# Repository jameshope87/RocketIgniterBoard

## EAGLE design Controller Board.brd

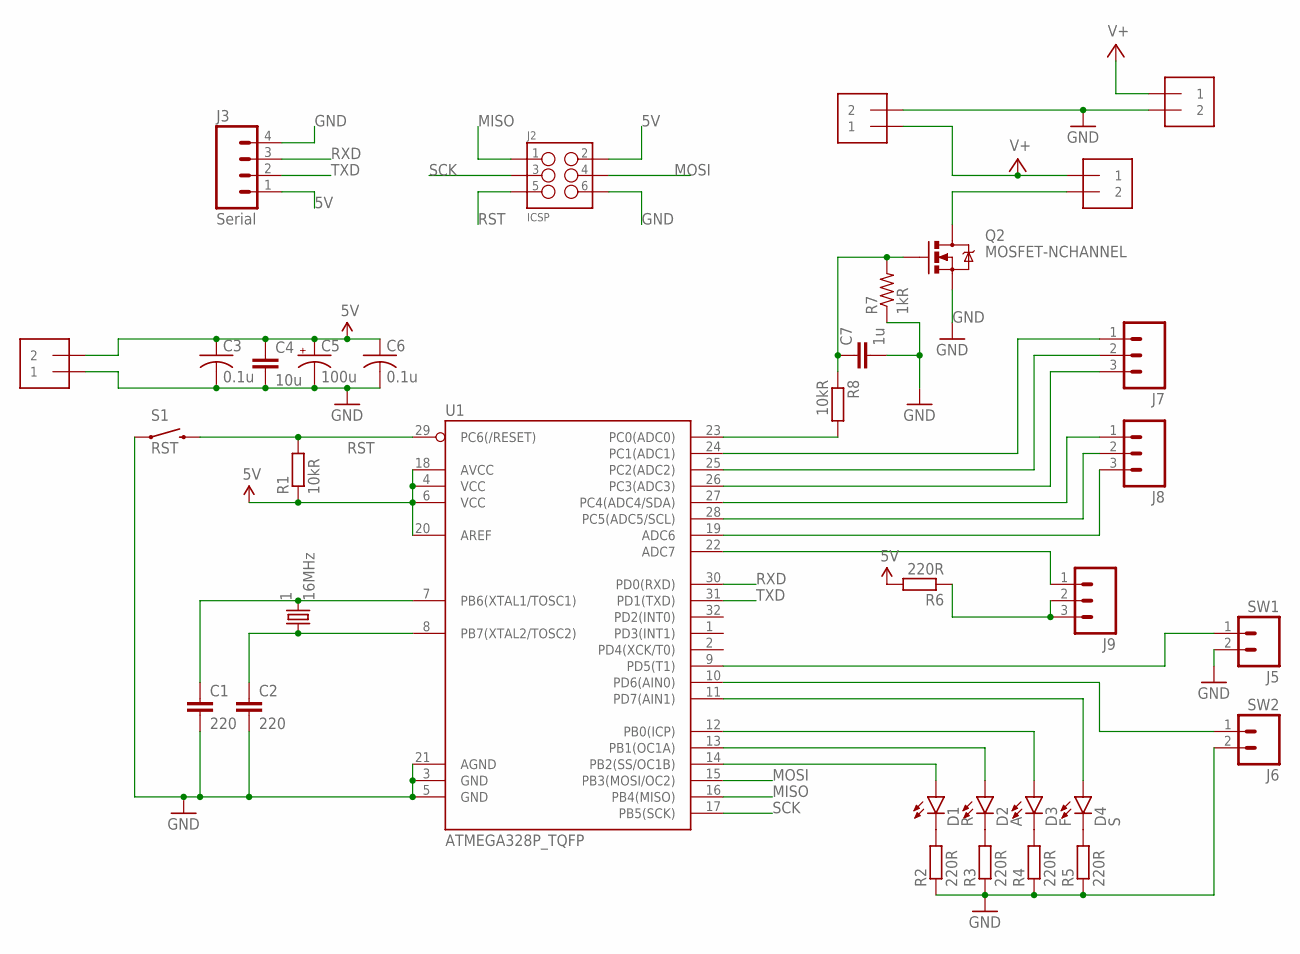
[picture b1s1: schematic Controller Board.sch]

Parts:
1: 16MHz; CRYSTAL-OSC-SMD-5X3.2
C1, C2: 220; C0603
C3, C6: 0.1u; C0603
C4: 10u; 0603-CAP
C5: 100u; PANASONIC_D
C7: 1u; 0603-CAP
D1: R; LED5MM
D2: A; LED5MM
D3: F; LED5MM
D4: S; LED5MM
FAN: FAN; 1X2-3.5MM
HV: HV; 1X2-3.5MM
J2: ICSP; 2X3
J3: Serial; 1X04
J5: SW1; 1X02_POLAR
J6: SW2; 1X02_POLAR
J7, J8, J9: M03PTH; 1X03
POWER: +5V; 1X2-3.5MM
Q2: MOSFET-NCHANNEL; TO220V
R1, R8: 10kR; R0603
R2, R3, R4, R5, R6: 220R; R0603
R7: 1kR; 0603-RES
S1: RST; TACTILE-SWITCH-1101NE
U1: ATMEGA328P_TQFP; TQFP32-08
V+: V+; 1X2-3.5MM

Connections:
5V: C3.1, C4.1, C5.+, C6.1, J2.2, J3.1, POWER.2, R1.1, R6.2, U1.4 (VCC), U1.6 (VCC), U1.18 (AVCC), U1.20 (AREF)
A: J7.1, U1.24 (PC1(ADC1))
B: J7.2, U1.25 (PC2(ADC2))
C: J7.3, U1.26 (PC3(ADC3))
D: J8.1, U1.27 (PC4(ADC4/SDA))
E: J8.2, U1.28 (PC5(ADC5/SCL))
F: J8.3, U1.19 (ADC6)
G: J9.1, U1.22 (ADC7)
GND: C1.2, C2.2, C3.2, C4.2, C5.-, C6.2, C7.2, FAN.2, J2.6, J3.4, J5.2, J6.2, POWER.1, Q2.3 (S), R2.1, R3.1, R4.1, R5.1, R7.1, S1.1, U1.3 (GND), U1.5 (GND), U1.21 (AGND), V+.2
MISO: J2.1, U1.16 (PB4(MISO))
MOSI: J2.4, U1.15 (PB3(MOSI/OC2))
unnamed: 1.3 (2), C1.1, U1.7 (PB6(XTAL1/TOSC1))
unnamed: 1.1, C2.1, U1.8 (PB7(XTAL2/TOSC2))
unnamed: D1.K (C), R2.2
unnamed: D2.K (C), R3.2
unnamed: D3.K (C), R4.2
unnamed: D1.A, U1.14 (PB2(SS/OC1B))
unnamed: D2.A, U1.13 (PB1(OC1A))
unnamed: D3.A, U1.12 (PB0(ICP))
unnamed: R8.2, U1.23 (PC0(ADC0))
unnamed: C7.1, Q2.1 (G), R7.2, R8.1
unnamed: D4.K (C), R5.2
unnamed: D4.A, U1.11 (PD7(AIN1))
unnamed: HV.2, Q2.2 (D)
unnamed: J6.1, U1.10 (PD6(AIN0))
unnamed: J5.1, U1.9 (PD5(T1))
unnamed: J9.2, J9.3, R6.1
RST: J2.5, R1.2, S1.2, U1.29 (PC6(/RESET))
RXD: J3.3, U1.30 (PD0(RXD))
SCK: J2.3, U1.17 (PB5(SCK))
TXD: J3.2, U1.31 (PD1(TXD))
V+: FAN.1, HV.1, V+.1

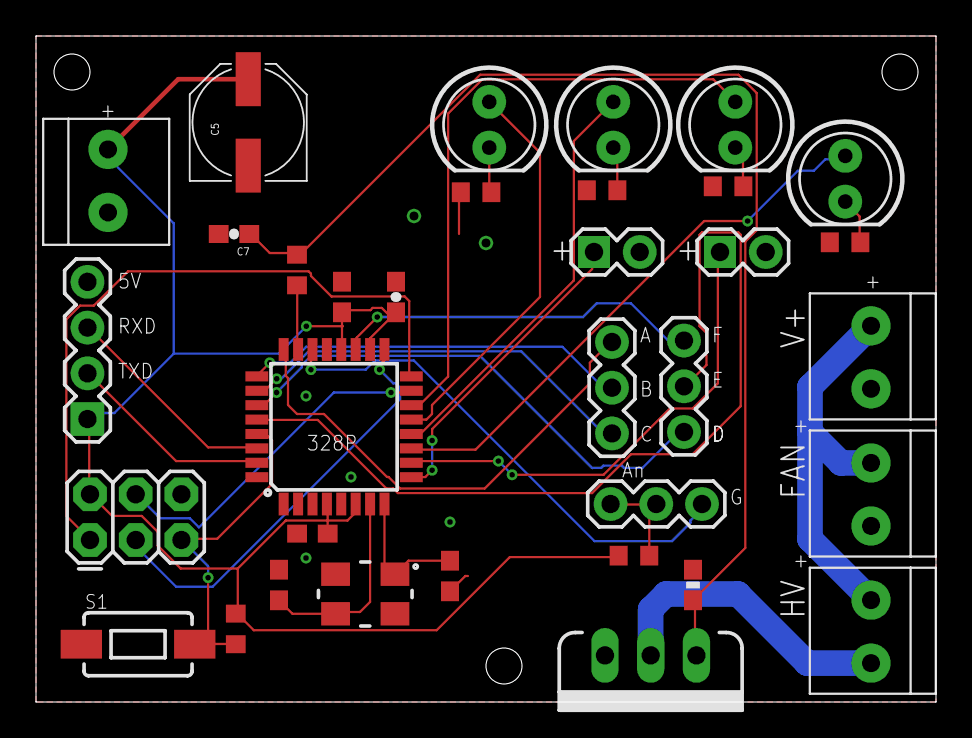
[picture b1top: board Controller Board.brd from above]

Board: 2 copper layers, 50.0 x 37.0 mm, 34 parts (0 on the bottom side), 32 nets.

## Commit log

2017-02-23 Create test

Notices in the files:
parts and their libraries:
SparkFun-Capacitors: Licensing: Creative Commons ShareAlike 4.0 International - https://creativecommons.org/licenses/by-sa/4.0
